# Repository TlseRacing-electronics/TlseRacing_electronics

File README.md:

# TlseRacing_electronics
all shematique and PCB

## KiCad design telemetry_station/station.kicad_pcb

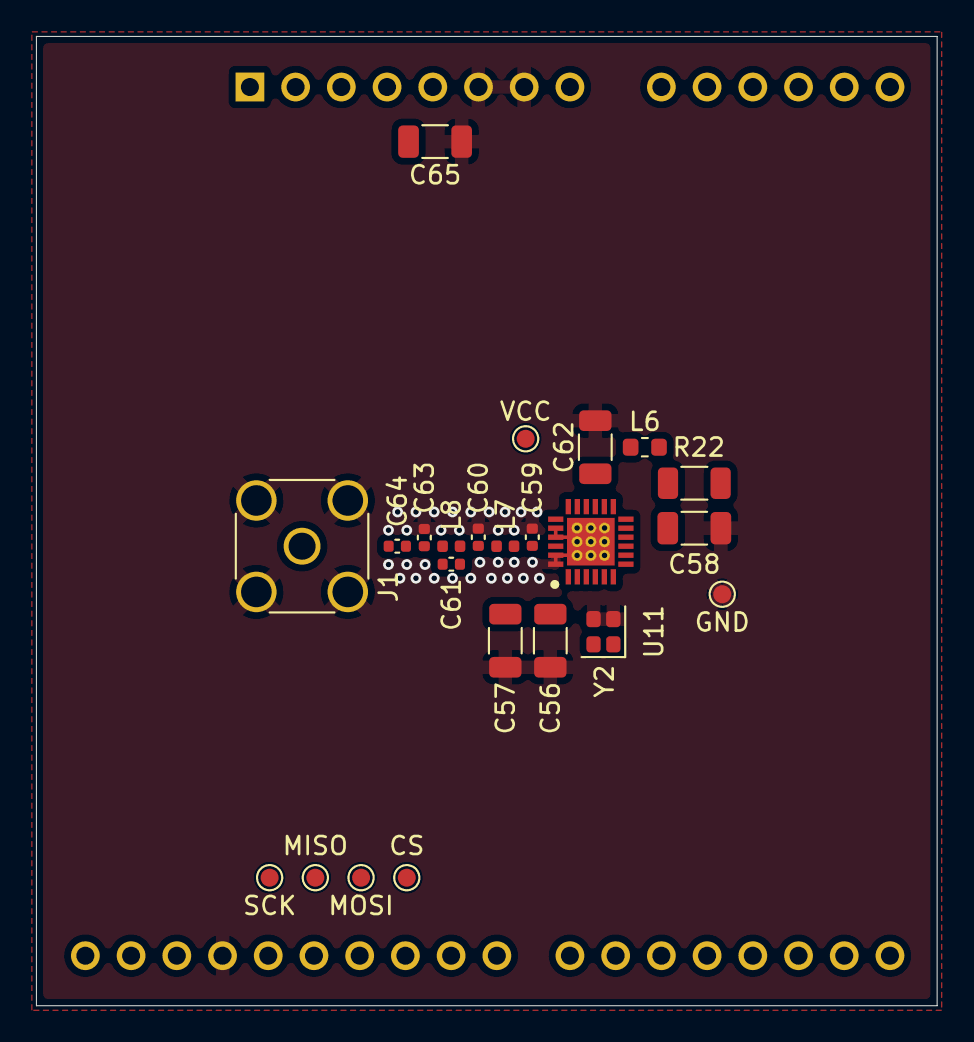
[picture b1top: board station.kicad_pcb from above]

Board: 4 copper layers, 50.0 x 53.8 mm, 24 parts (0 on the bottom side), 21 nets.

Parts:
A1: Arduino_UNO_R3
C56, C57: 10nF; C_1206_3216Metric
C58, C62: 100nF; C_1206_3216Metric
C59: 0.8pF; C_0402_1005Metric
C60, C63: 1.2pF; C_0402_1005Metric
C61: 0.5pF; C_0402_1005Metric
C64: 100pF; C_0402_1005Metric
C65: 10uF; C_1206_3216Metric
J1: 2.4Ghz; SMA_Amphenol_132134_Vertical
L6: 15uH; L_0603_1608Metric
L7: 3nH; L_0402_1005Metric
L8: 2.5nH; L_0402_1005Metric
R22: 0; R_1206_3216Metric
TP1: CS; TestPoint_Pad_D1.0mm
TP2: MOSI; TestPoint_Pad_D1.0mm
TP3: MISO; TestPoint_Pad_D1.0mm
TP4: SCK; TestPoint_Pad_D1.0mm
TP5: VCC; TestPoint_Pad_D1.0mm
TP6: GND; TestPoint_Pad_D1.0mm
U11: SX1280IMLTRT; QFN50P400X400X100-25N-D
Y2: 52Mhz; Crystal_SMD_2016-4Pin_2.0x1.6mm

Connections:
/CS_SX1280: A1.25 (D10), TP1.1 (1_1), U11.19 (NSS_CTS)
/DCC_SW: C56.2, L6.2, U11.2 (VDD_IN), U11.12 (DCC_FB)
/MISO_SX1280: A1.27 (D12), TP3.1 (1_1), U11.16 (MISO_TX)
/MOSI_SX1280: A1.26 (D11), TP2.1 (1_1), U11.17 (MOSI_RX)
/SCK_SX1280: A1.28 (D13), TP4.1 (1_1), U11.18 (SCK_RTSN)
/SX1280_BUSY: A1.18 (D3), U11.7 (BUSY)
/SX1280_DIO1: A1.19 (D4), U11.8 (DIO1)
/SX1280_DIO2: A1.20 (D5), U11.9 (DIO2)
/SX1280_DIO3: A1.21 (D6), U11.10 (DIO3)
/SX1280_RESET: A1.17 (D2), U11.3 (NRESET)
GND: A1.6 (GND), A1.7 (GND), A1.29 (GND), C56.1, C57.1, C58.1, C59.1, C60.1, C62.1, C63.1, C65.1, J1.2 (Ext), TP6.1 (1_1), U11.5 (GND_1), U11.13 (GND_2), U11.20 (GND_3), U11.21 (GND_4), U11.23 (GND_5), U11.24 (GND_6), U11.25, Y2.2 (G), Y2.3 (G)
unnamed: C60.2, C61.2, L7.2, L8.1
unnamed: C61.1, C63.2, C64.2, L8.2
unnamed: C64.1, J1.1 (In)
unnamed: L6.1, U11.14 (DCC_SW)
unnamed: C59.2, L7.1, U11.22 (RFIO)
unnamed: C58.2, R22.2, U11.11 (VBAT_IO)
unnamed: C57.2, U11.1 (VR_PA)
unnamed: U11.4 (XTA), Y2.4
unnamed: U11.6 (XTB), Y2.1
VCC: A1.4 (3V3), C62.2, C65.2, R22.1, TP5.1 (1_1), U11.15 (VBAT)

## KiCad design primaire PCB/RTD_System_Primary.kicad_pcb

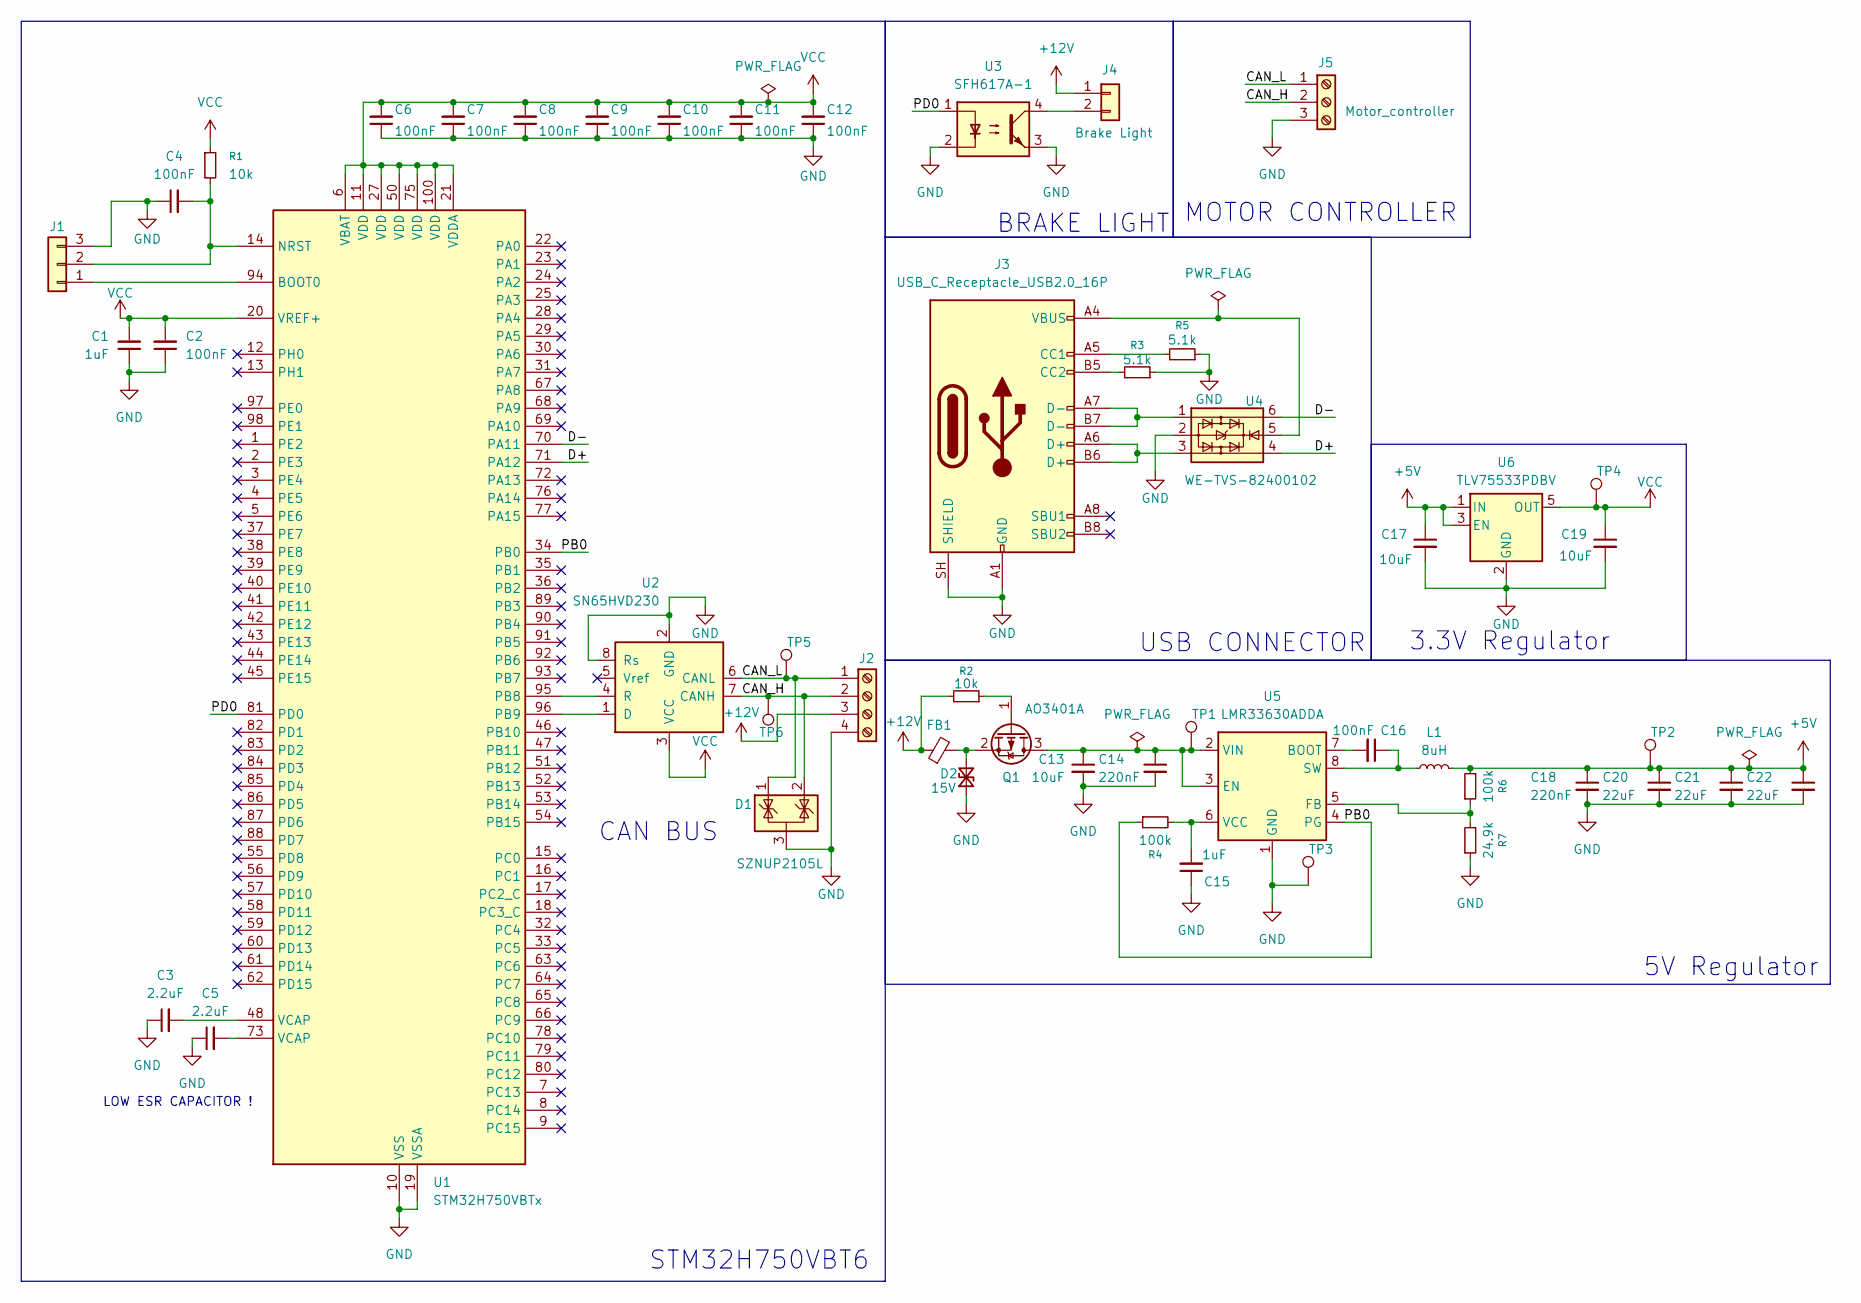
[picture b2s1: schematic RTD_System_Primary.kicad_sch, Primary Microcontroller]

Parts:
C1, C15: 1uF; C_1206_3216Metric
C2, C4, C6, C7, C8, C9, C10, C11, C12, C16: 100nF; C_1206_3216Metric
C3, C5: 2.2uF; C_1206_3216Metric
C13, C17, C19: 10uF; C_1206_3216Metric
C14, C18: 220nF; C_1206_3216Metric
C20, C21, C22: 22uF; C_1206_3216Metric
D1: SZNUP2105L; SOT-23
D2: 15V; TSOT-23
FB1: FerriteBead_Small; R_1206_3216Metric
J1: Conn_01x03; JST_XH_B3B-XH-A_1x03_P2.50mm_Vertical
J2: Screw_Terminal_01x04; TerminalBlock_Phoenix_MKDS-1,5-4_1x04_P5.00mm_Horizontal
J3: USB_C_Receptacle_USB2.0_16P; USB_C_Receptacle_GCT_USB4105-xx-A_16P_TopMnt_Horizontal
J4: Brake Light; JST_XH_B2B-XH-A_1x02_P2.50mm_Vertical
J5: Motor_controller; TerminalBlock_Phoenix_MKDS-1,5-3-5.08_1x03_P5.08mm_Horizont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
L1: 8uH; L_1206_3216Metric
Q1: AO3401A; SOT-23
R1, R2: 10k; R_1206_3216Metric
R3, R5: 5.1k; R_1206_3216Metric
R4, R6: 100k; R_1206_3216Metric
R7: 24.9k; R_1206_3216Metric
TP1: 12V; TestPoint_THTPad_1.0x1.0mm_Drill0.5mm
TP2: 5V; TestPoint_THTPad_1.0x1.0mm_Drill0.5mm
TP3: GND; TestPoint_THTPad_1.0x1.0mm_Drill0.5mm
TP4: VCC; TestPoint_THTPad_1.0x1.0mm_Drill0.5mm
TP5: CANL; TestPoint_THTPad_1.0x1.0mm_Drill0.5mm
TP6: CANH; TestPoint_THTPad_1.0x1.0mm_Drill0.5mm
U1: STM32H750VBTx; LQFP-100_14x14mm_P0.5mm
U2: SN65HVD230; SOIC-8_3.9x4.9mm_P1.27mm
U3: SFH617A-1; DIP-4_W7.62mm
U4: WE-TVS-82400102; SOT-23-6
U5: LMR33630ADDA; Texas_HSOP-8-1EP_3.9x4.9mm_P1.27mm_ThermalVias
U6: TLV75533PDBV; SOT-23-5

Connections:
+5V: C17.1, C18.1, C20.1, C21.1, C22.1, L1.2, R6.2, TP2.1 (1_1), U6.1 (IN), U6.3 (EN)
+12V: FB1.1, J2.3, J4.1, R2.2
/CAN_H: D1.2 (K), J2.2, J5.2, TP6.1 (1_1), U2.7 (CANH)
/CAN_L: D1.1 (K), J2.1, J5.1, TP5.1 (1_1), U2.6 (CANL)
/D+: U1.71 (PA12), U4.4
/D-: U1.70 (PA11), U4.6
/PB0: R4.1, U1.34 (PB0), U5.4 (PG)
/PD0: U1.81 (PD0), U3.1
GND: C1.1, C2.1, C3.1, C4.1, C5.1, C6.1, C7.1, C8.1, C9.1, C10.1, C11.1, C12.1, C13.2, C14.2, C15.1, C17.2, C18.2, C19.2, C20.2, C21.2, C22.2, D1.3 (A), D2.1 (A1), J1.3, J2.4, J3.A1 (GND), J3.A12 (GND), J3.B1 (GND), J3.B12 (GND), J3.SH (SHIELD), J5.3, R3.1, R5.1, R7.1, TP3.1 (1_1), U1.10 (VSS), U1.19 (VSSA), U1.26 (VSS), U1.49 (VSS), U1.74 (VSS), U1.99 (VSS), U2.2 (GND), U2.8 (Rs), U3.2, U3.3, U4.2, U5.1 (GND), U5.9 (GND), U6.2 (GND)
unnamed: C3.2, U1.48 (VCAP)
unnamed: C5.2, U1.73 (VCAP)
unnamed: D2.2 (A2), FB1.2, Q1.2 (S)
unnamed: J1.1, U1.94 (BOOT0)
unnamed: C4.2, J1.2, R1.2, U1.14 (NRST)
unnamed: J3.A5 (CC1), R5.2
unnamed: J3.B5 (CC2), R3.2
unnamed: J3.A6 (D+), J3.B6 (D+), U4.3
unnamed: J3.A7 (D-), J3.B7 (D-), U4.1
unnamed: J3.A4 (VBUS), J3.A9 (VBUS), J3.B4 (VBUS), J3.B9 (VBUS), U4.5
unnamed: J4.2, U3.4
unnamed: C13.1, C14.1, Q1.3 (D), TP1.1 (1_1), U5.2 (VIN), U5.3 (EN)
unnamed: Q1.1 (G), R2.1
unnamed: U1.95 (PB8), U2.4 (R)
unnamed: U1.96 (PB9), U2.1 (D)
unnamed: C16.2, U5.7 (BOOT)
unnamed: R6.1, R7.2, U5.5 (FB)
unnamed: C16.1, L1.1, U5.8 (SW)
unnamed: C15.2, R4.2, U5.6 (VCC)
VCC: C1.2, C2.2, C6.2, C7.2, C8.2, C9.2, C10.2, C11.2, C12.2, C19.1, R1.1, TP4.1 (1_1), U1.6 (VBAT), U1.11 (VDD), U1.20 (VREF+), U1.21 (VDDA), U1.27 (VDD), U1.50 (VDD), U1.75 (VDD), U1.100 (VDD), U2.3 (VCC), U6.5 (OUT)

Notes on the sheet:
LOW ESR CAPACITOR !
STM32H750VBT6
CAN BUS
BRAKE LIGHT
3.3V Regulator
MOTOR CONTROLLER
USB CONNECTOR
5V Regulator

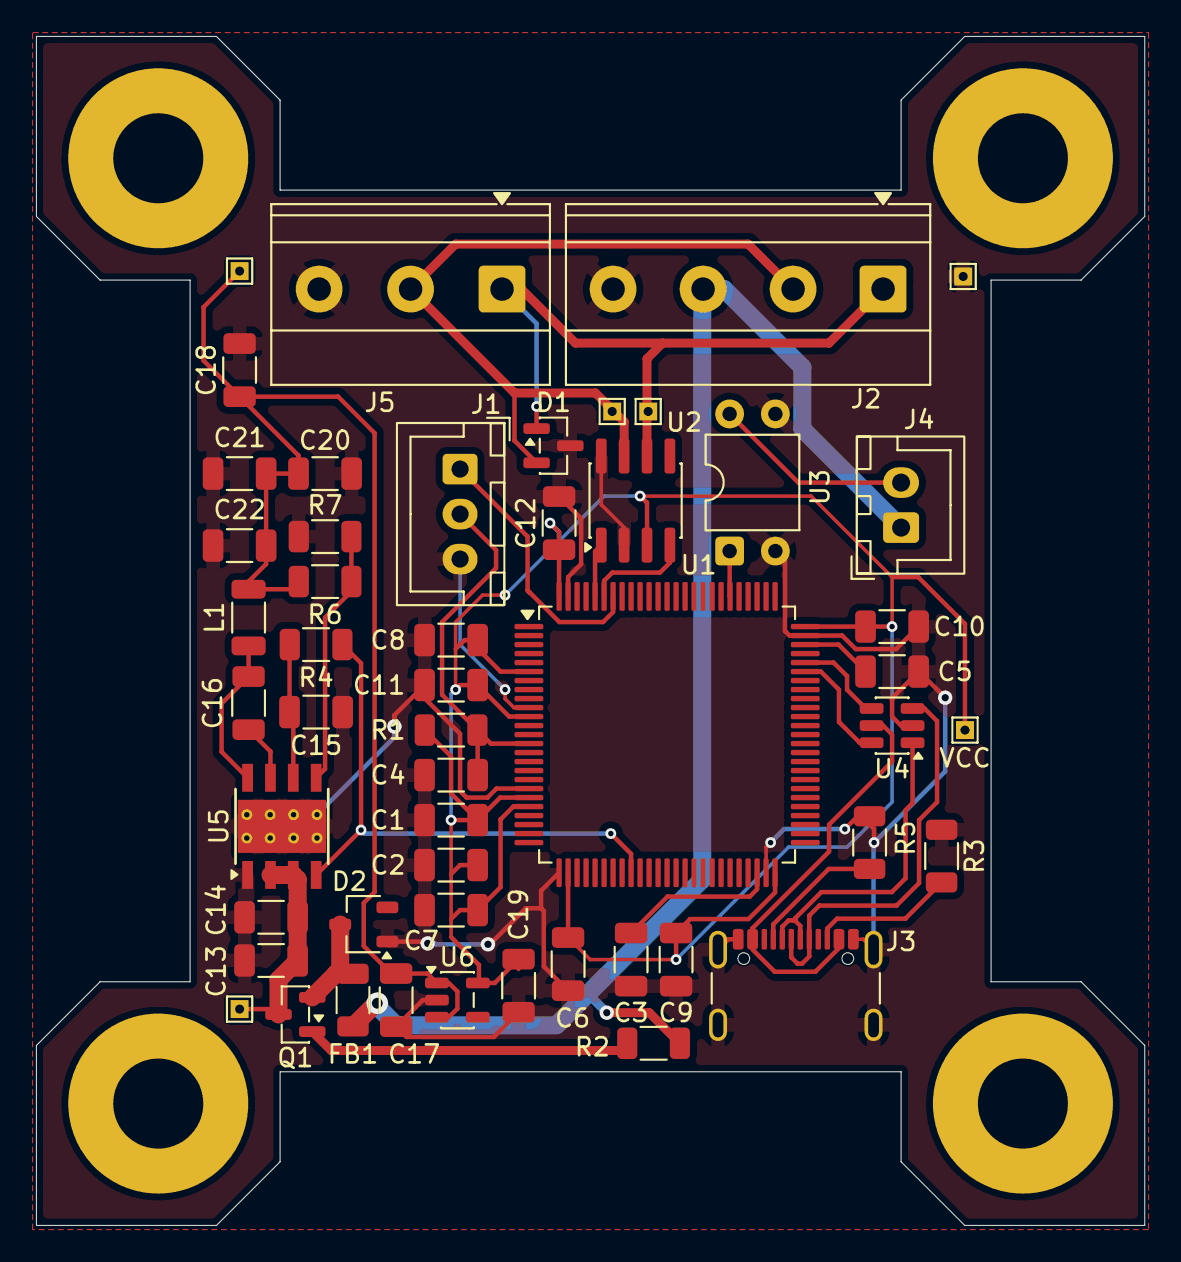
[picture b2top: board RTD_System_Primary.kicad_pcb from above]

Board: 2 copper layers, 61.6 x 66.1 mm, 51 parts (0 on the bottom side), 29 nets.

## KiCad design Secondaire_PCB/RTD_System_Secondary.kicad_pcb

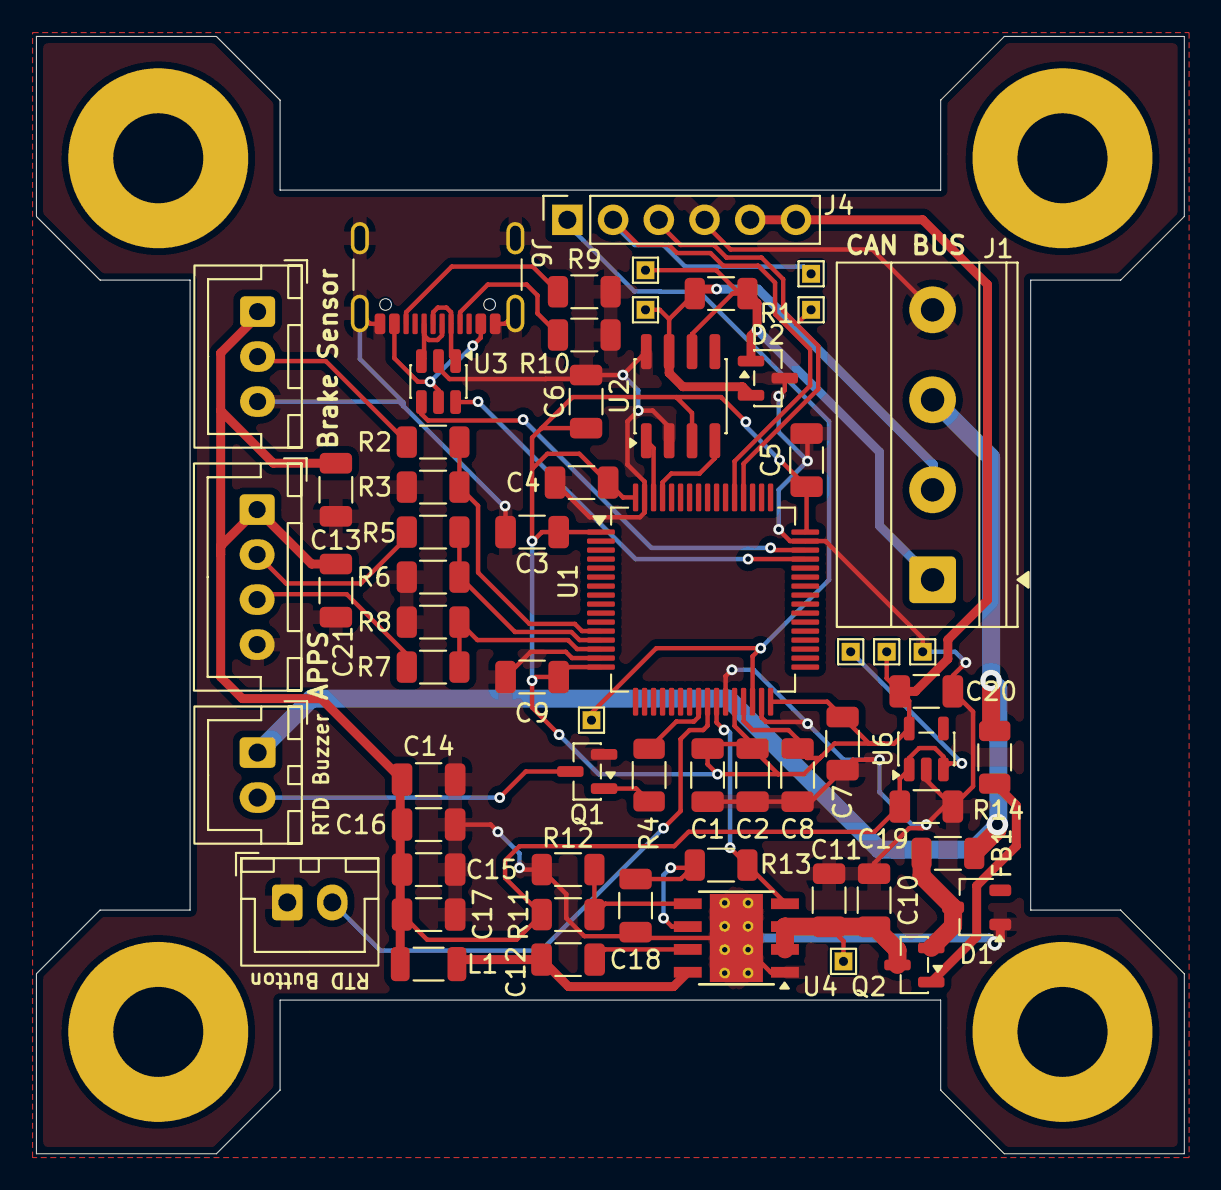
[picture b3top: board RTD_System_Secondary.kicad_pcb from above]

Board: 2 copper layers, 63.8 x 62.1 mm, 62 parts (0 on the bottom side), 36 nets.

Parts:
5V, 12V: TestPoint; TestPoint_THTPad_1.0x1.0mm_Drill0.5mm
BZ1: Buzzer; JST_XH_B2B-XH-A_1x02_P2.50mm_Vertical
C1, C18: 1uF; C_1206_3216Metric
C2, C3, C4, C5, C6, C7, C8, C9, C12: 100nF; C_1206_3216Metric
C10, C13, C19, C20, C21: 10uF; C_1206_3216Metric
C11, C14: 220nF; C_1206_3216Metric
C15, C16, C17: 22uF; C_1206_3216Metric
CANH: TestPoint; TestPoint_THTPad_1.0x1.0mm_Drill0.5mm
CANL: TestPoint; TestPoint_THTPad_1.0x1.0mm_Drill0.5mm
D1: 15V; TSOT-23
D2: SZNUP2105L; SOT-23
FB1: FerriteBead_Small; R_1206_3216Metric
GND: TestPoint; TestPoint_THTPad_1.0x1.0mm_Drill0.5mm
J1: Screw_Terminal_01x04; TerminalBlock_Phoenix_MKDS-1,5-4_1x04_P5.00mm_Horizontal
J2: Brake_Sensor; JST_XH_B3B-XH-A_1x03_P2.50mm_Vertical
J3: RTD Button; JST_XH_B2B-XH-A_1x02_P2.50mm_Vertical
J4: Conn_01x06; PinSocket_1x06_P2.54mm_Vertical
J5: APPS; JST_XH_B4B-XH-A_1x04_P2.50mm_Vertical
J6: USB_C_Receptacle_USB2.0_16P; USB_C_Receptacle_GCT_USB4105-xx-A_16P_TopMnt_Horizontal
L1: 8uH; L_1206_3216Metric
PB10: TestPoint; TestPoint_THTPad_1.0x1.0mm_Drill0.5mm
Q1: AO3400A; SOT-23
Q2: AO3401A; SOT-23
R1: 120; R_1206_3216Metric
R2, R5, R7: 3.9k; R_1206_3216Metric
R3, R6, R8, R14: 10k; R_1206_3216Metric
R4: 100; R_1206_3216Metric
R9, R10: 5.1k; R_1206_3216Metric
R11, R13: 100k; R_1206_3216Metric
R12: 24.9k; R_1206_3216Metric
RXD: TestPoint; TestPoint_THTPad_1.0x1.0mm_Drill0.5mm
TXD: TestPoint; TestPoint_THTPad_1.0x1.0mm_Drill0.5mm
U1: STM32G474RETx; LQFP-64_10x10mm_P0.5mm
U2: SN65HVD230; SOIC-8_3.9x4.9mm_P1.27mm
U3: WE-TVS-82400102; SOT-23-6
U4: LMR33630ADDA; Texas_HSOP-8-1EP_3.9x4.9mm_P1.27mm_ThermalVias
U6: TLV75533PDBV; SOT-23-5
VCC: TestPoint; TestPoint_THTPad_1.0x1.0mm_Drill0.5mm

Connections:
+5V: 5V.1 (1_1), C13.2, C14.1, C15.1, C16.1, C17.1, C19.1, C21.2, J2.1, J5.1, L1.2, R11.2, U6.1 (IN), U6.3 (EN)
+12V: BZ1.1 (+), FB1.1, J1.3, R14.2
/D+: U1.46 (PA12), U3.4
/D-: U1.45 (PA11), U3.6
/PA0: R2.2, R3.1, U1.12 (PA0)
/PA1: R5.2, R6.1, U1.13 (PA1)
/PA2: R7.2, R8.1, U1.14 (PA2)
/PB0: R4.1, U1.24 (PB0)
/PB1: J3.2, U1.25 (PB1)
/PB2: R13.1, U1.26 (PB2), U4.4 (PG)
/PB10: J4.1, PB10.1 (1_1), U1.30 (PB10)
/RXD: J4.2, RXD.1 (1_1), U1.53 (PC11)
/TXD: J4.3, TXD.1 (1_1), U1.52 (PC10)
GND: C1.1, C2.1, C3.1, C4.1, C5.1, C6.2, C7.1, C8.1, C9.1, C10.2, C11.2, C13.1, C14.2, C15.2, C16.2, C17.2, C18.1, C19.2, C20.2, C21.1, D1.1 (A1), D2.3 (A), GND.1 (1_1), J1.4, J2.3, J3.1, J4.4, J5.4, J6.A1 (GND), J6.A12 (GND), J6.B1 (GND), J6.B12 (GND), J6.SH (SHIELD), Q1.2 (S), R3.2, R6.2, R8.2, R9.1, R10.1, R12.1, U1.15 (VSS), U1.27 (VSSA), U1.31 (VSS), U1.47 (VSS), U1.63 (VSS), U2.2 (GND), U2.8 (Rs), U3.2, U4.1 (GND), U4.9 (GND), U6.2 (GND)
unnamed: BZ1.2 (-), Q1.3 (D)
unnamed: D1.2 (A2), FB1.2, Q2.2 (S)
unnamed: CANL.1 (1_1), D2.1 (K), J1.1, R1.1, U2.6 (CANL)
unnamed: CANH.1 (1_1), D2.2 (K), J1.2, R1.2, U2.7 (CANH)
unnamed: J2.2, R2.1
unnamed: J5.2, R5.1
unnamed: J5.3, R7.1
unnamed: J6.A5 (CC1), R10.2
unnamed: J6.B5 (CC2), R9.2
unnamed: J6.A6 (D+), J6.B6 (D+), U3.3
unnamed: J6.A7 (D-), J6.B7 (D-), U3.1
unnamed: J6.A4 (VBUS), J6.A9 (VBUS), J6.B4 (VBUS), J6.B9 (VBUS), U3.5
unnamed: Q1.1 (G), R4.2
unnamed: 12V.1 (1_1), C10.1, C11.1, Q2.3 (D), U4.2 (VIN), U4.3 (EN)
unnamed: Q2.1 (G), R14.1
unnamed: U1.61 (PB8), U2.4 (R)
unnamed: U1.62 (PB9), U2.1 (D)
unnamed: C12.2, U4.7 (BOOT)
unnamed: R11.1, R12.2, U4.5 (FB)
unnamed: C12.1, L1.1, U4.8 (SW)
unnamed: C18.2, R13.2, U4.6 (VCC)
VCC: C1.2, C2.2, C3.2, C4.2, C5.2, C6.1, C7.2, C8.2, C9.2, C20.1, J4.5, J4.6, U1.1 (VBAT), U1.16 (VDD), U1.28 (VREF+), U1.29 (VDDA), U1.32 (VDD), U1.48 (VDD), U1.64 (VDD), U2.3 (VCC), U6.5 (OUT), VCC.1 (1_1)
